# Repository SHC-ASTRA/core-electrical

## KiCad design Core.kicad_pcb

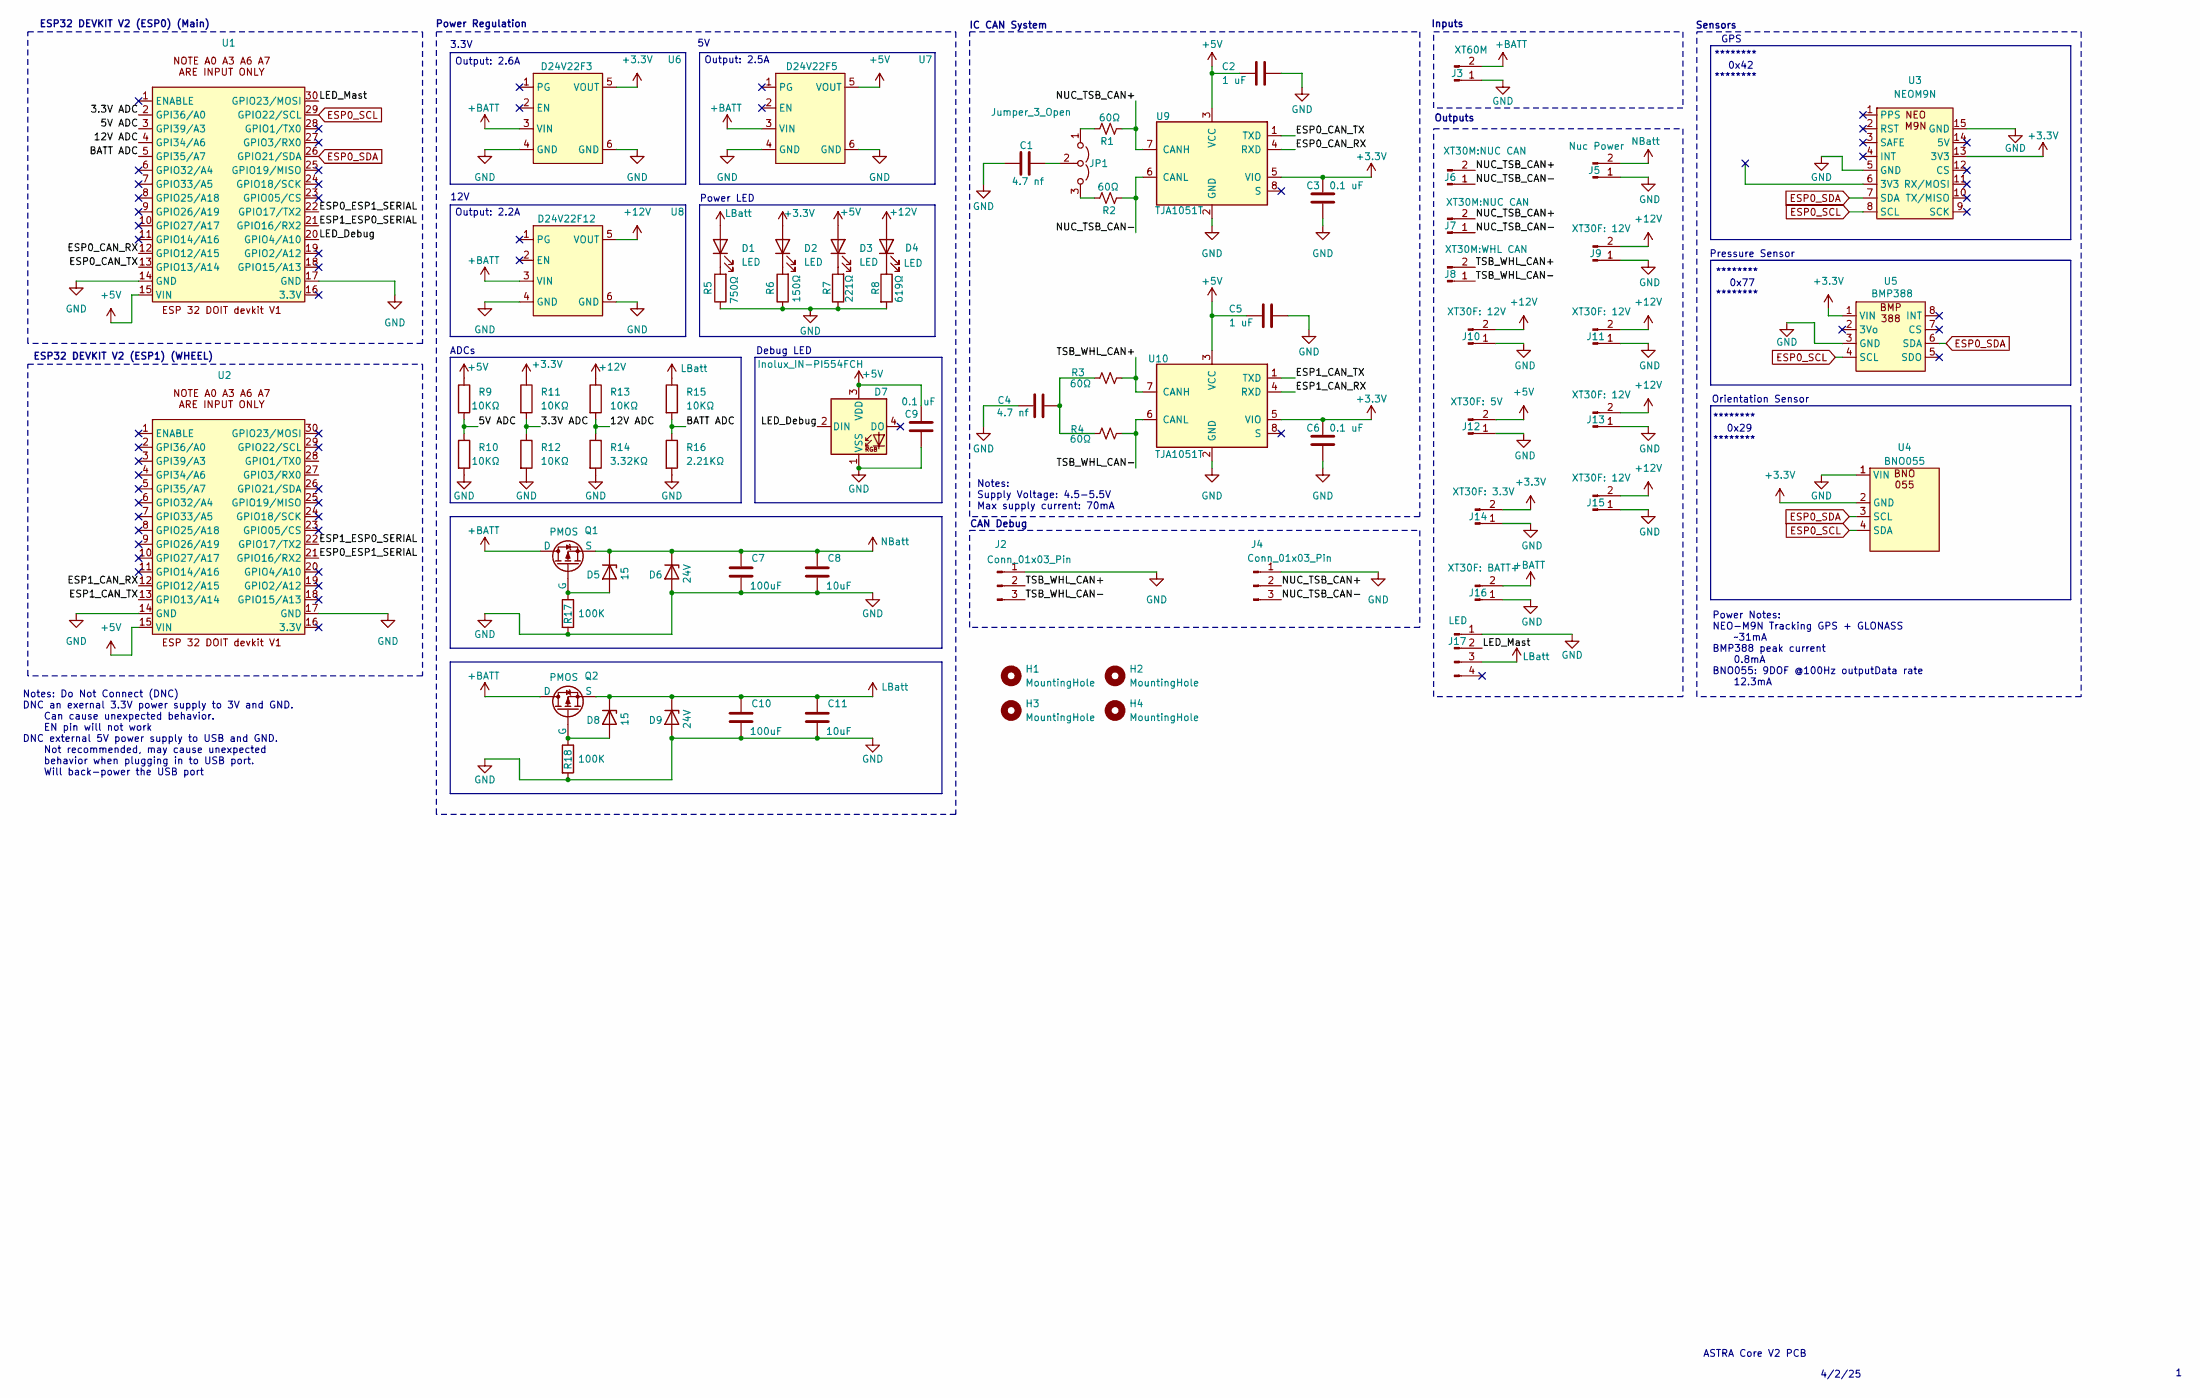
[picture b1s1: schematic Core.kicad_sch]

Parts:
C1, C4: 4.7 nf; C_0603_1608Metric_Pad1.08x0.95mm_HandSolder
C2, C5: 1 uF; C_0603_1608Metric_Pad1.08x0.95mm_HandSolder
C3, C6, C9: 0.1 uF; C_0603_1608Metric_Pad1.08x0.95mm_HandSolder
C7, C10: 100uF; C_0603_1608Metric_Pad1.08x0.95mm_HandSolder
C8, C11: 10uF; C_0603_1608Metric_Pad1.08x0.95mm_HandSolder
D1, D2, D3, D4: LED; LED 3mm
D5, D8: 15; D_SOD-123
D6, D9: 24V; TVS_CUHZ20VH3F
D7: Inolux_IN-PI554FCH; LED_Inolux_IN-PI554FCH_PLCC4_5.0x5.0mm_P3.2mm
H1, H2, H3, H4: MountingHole; 3mm Hole
J2, J4: Conn_01x03_Pin; PinHeader_1x03_P2.54mm_Vertical
J3: XT60M; AMASS_XT60PW-M_1x02_P7.20mm_Horizontal
J5: Nuc Power; Molex_Mini-Fit_Jr_5569-02A2_2x01_P4.20mm_Horizontal
J6, J7: XT30M:NUC CAN; XT30M_MODIFIED
J8: XT30M:WHL CAN; XT30M_MODIFIED
J9, J10, J11, J13, J15: XT30F: 12V; XT30F_MODIFIED
J12: XT30F: 5V; XT30F_MODIFIED
J14: XT30F: 3.3V; XT30F_MODIFIED
J16: XT30F: BATT+; XT30F_MODIFIED
J17: LED; Molex_Mini-Fit_Jr__2x02_Horizontal
JP1: Jumper_3_Open; PinHeader_1x03_P2.54mm_Vertical
Q1, Q2: PMOS; TO-252-2
R1, R2, R3, R4: 60Ω; R_0603_1608Metric_Pad0.98x0.95mm_HandSolder
R5: 750Ω; R_0603_1608Metric_Pad0.98x0.95mm_HandSolder
R6: 150Ω; R_0603_1608Metric_Pad0.98x0.95mm_HandSolder
R7: 221Ω; R_0603_1608Metric_Pad0.98x0.95mm_HandSolder
R8: 619Ω; R_0603_1608Metric_Pad0.98x0.95mm_HandSolder
R9, R10, R11, R12, R13, R15: 10KΩ; R_0603_1608Metric_Pad0.98x0.95mm_HandSolder
R14: 3.32KΩ; R_0603_1608Metric_Pad0.98x0.95mm_HandSolder
R16: 2.21KΩ; R_0603_1608Metric_Pad0.98x0.95mm_HandSolder
R17, R18: 100K; C_0603_1608Metric_Pad1.08x0.95mm_HandSolder
U1, U2: esp32_devkit_v1
U3: NEOM9N; NEO-M9N
U4: BNO055; Molex_Mini-Fit_Jr__2x02_Horizontal
U5: BMP388
U6: D24V22F3; D24V22Fx
U7: D24V22F5; D24V22Fx
U8: D24V22F12; D24V22Fx
U9, U10: TJA1051T; SOIC-8_3.9x4.9mm_P1.27mm

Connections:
+3.3V: C3.1, C6.1, D2.2 (A), J14.2 (Pin_1), R11.1, U3.13 (3V3), U4.2 (GND), U5.1 (VIN), U6.5 (VOUT), U9.5 (VIO), U10.5 (VIO)
+5V: C2.2, C5.2, C9.1, D3.2 (A), D7.3 (VDD), J12.2 (Pin_1), R9.1, U1.15 (VIN), U2.15 (VIN), U7.5 (VOUT), U9.3 (VCC), U10.3 (VCC)
+12V: D4.2 (A), J9.2 (Pin_1), J10.2 (Pin_1), J11.2 (Pin_1), J13.2 (Pin_1), J15.2 (Pin_1), R13.1, U8.5 (VOUT)
+BATT: J3.2 (Pin_1), J16.2 (Pin_1), Q1.1 (D), Q2.1 (D), U6.3 (VIN), U7.3 (VIN), U8.3 (VIN)
/3.3V ADC: R11.2, R12.1, U1.2 (GPI36/A0)
/5V ADC: R9.2, R10.1, U1.3 (GPI39/A3)
/12V ADC: R13.2, R14.1, U1.4 (GPI34/A6)
/BATT ADC: R15.2, R16.1, U1.5 (GPI35/A7)
/ESP0_CAN_RX: U1.12 (GPIO12/A15), U9.4 (RXD)
/ESP0_CAN_TX: U1.13 (GPIO13/A14), U9.1 (TXD)
/ESP0_ESP1_SERIAL: U1.22 (GPIO17/TX2), U2.21 (GPIO16/RX2)
/ESP1_CAN_RX: U2.12 (GPIO12/A15), U10.4 (RXD)
/ESP1_CAN_TX: U2.13 (GPIO13/A14), U10.1 (TXD)
/ESP1_ESP0_SERIAL: U1.21 (GPIO16/RX2), U2.22 (GPIO17/TX2)
/LED_Debug: D7.2 (DIN), U1.20 (GPIO4/A10)
/LED_Mast: J17.2, U1.30 (GPIO23/MOSI)
/NUC_TSB_CAN+: J4.2, J6.2 (Pin_1), J7.2 (Pin_1), R1.1, U9.7 (CANH)
/NUC_TSB_CAN-: J4.3, J6.1 (Pin_2), J7.1 (Pin_2), R2.2, U9.6 (CANL)
/TSB_WHL_CAN+: J2.2, J8.2 (Pin_1), R3.1, U10.7 (CANH)
/TSB_WHL_CAN-: J2.3, J8.1 (Pin_2), R4.2, U10.6 (CANL)
ESP0_SCL: U1.29 (GPIO22/SCL), U3.8 (SCL), U4.4 (SDA), U5.4 (SCL)
ESP0_SDA: U1.26 (GPIO21/SDA), U3.7 (SDA), U4.3 (SCL), U5.6 (SDA)
GND: C1.1, C2.1, C3.2, C4.1, C5.1, C6.2, C7.2, C8.2, C9.2, C10.2, C11.2, D6.2 (A), D7.1 (VSS), D9.2 (A), J2.1, J3.1 (Pin_2), J4.1, J5.1 (Pin_2), J9.1 (Pin_2), J10.1 (Pin_2), J11.1 (Pin_2), J12.1 (Pin_2), J13.1 (Pin_2), J14.1 (Pin_2), J15.1 (Pin_2), J16.1 (Pin_2), J17.1, R5.1, R6.1, R7.1, R8.2, R10.2, R12.2, R14.2, R16.2, R17.2, R18.2, U1.14 (GND), U1.17 (GND), U2.14 (GND), U2.17 (GND), U3.5 (GND), U3.15 (GND), U4.1 (VIN), U5.3 (GND), U6.4 (GND), U6.6 (GND), U7.4 (GND), U7.6 (GND), U8.4 (GND), U8.6 (GND), U9.2 (GND), U10.2 (GND)
LBatt: C10.1, C11.1, D1.2 (A), D8.1 (K), D9.1 (K), J17.3, Q2.3 (S), R15.1
NBatt: C7.1, C8.1, D5.1 (K), D6.1 (K), J5.2 (Pin_1), Q1.3 (S)
unnamed: C4.2, R3.2, R4.1
unnamed: D1.1 (K), R5.2
unnamed: D2.1 (K), R6.2
unnamed: D3.1 (K), R7.2
unnamed: D4.1 (K), R8.1
unnamed: D5.2 (A), Q1.2 (G), R17.1
unnamed: D8.2 (A), Q2.2 (G), R18.1
unnamed: JP1.1 (A), R1.2
unnamed: JP1.3 (B), R2.1
unnamed: C1.2, JP1.2 (C)

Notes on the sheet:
******** 0x29 ********
ASTRA Core V2 PCB
ESP32 DEVKIT V2 (ESP0) (Main)
IC CAN System
Power Notes: NEO-M9N Tracking GPS + GLONASS ~31mA BMP388 peak current 0.8mA BNO055: 9DOF @100Hz outputData rate 12.3mA
ESP32 DEVKIT V2 (ESP1) (WHEEL)
Output: 2.2A
Output: 2.5A
Power Regulation
******** 0x42 ********
Orientation Sensor
Outputs
Debug LED
Notes: Supply Voltage: 4.5-5.5V Max supply current: 70mA
3.3V
GPS
ADCs
Sensors
12V
Pressure Sensor
******** 0x77 ********
CAN Debug
Notes: Do Not Connect (DNC) DNC an exernal 3.3V power supply to 3V and GND. Can cause unexpected behavior. EN pin will not work DNC external 5V power supply to USB and GND. Not recommended, may cause unexpected behavior when plugging in to USB port. Will back-power the USB port
Inputs
Output: 2.6A
4/2/25
Power LED

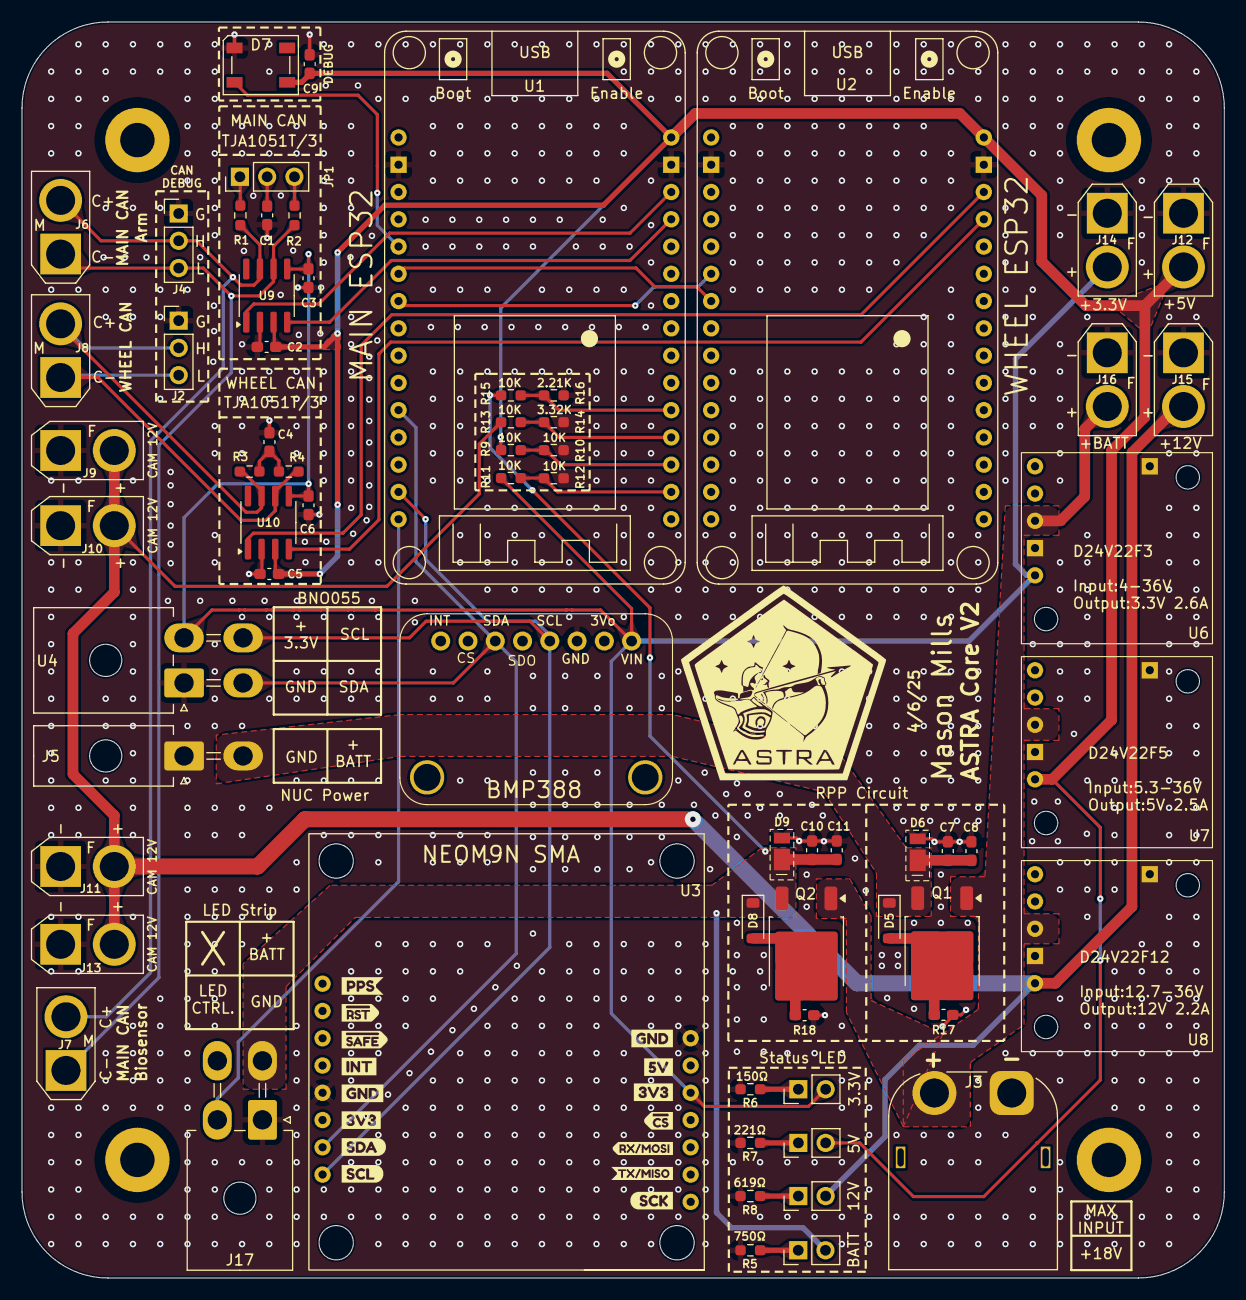
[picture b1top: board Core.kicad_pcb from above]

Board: 2 copper layers, 112.0 x 117.0 mm, 71 parts (0 on the bottom side), 35 nets.

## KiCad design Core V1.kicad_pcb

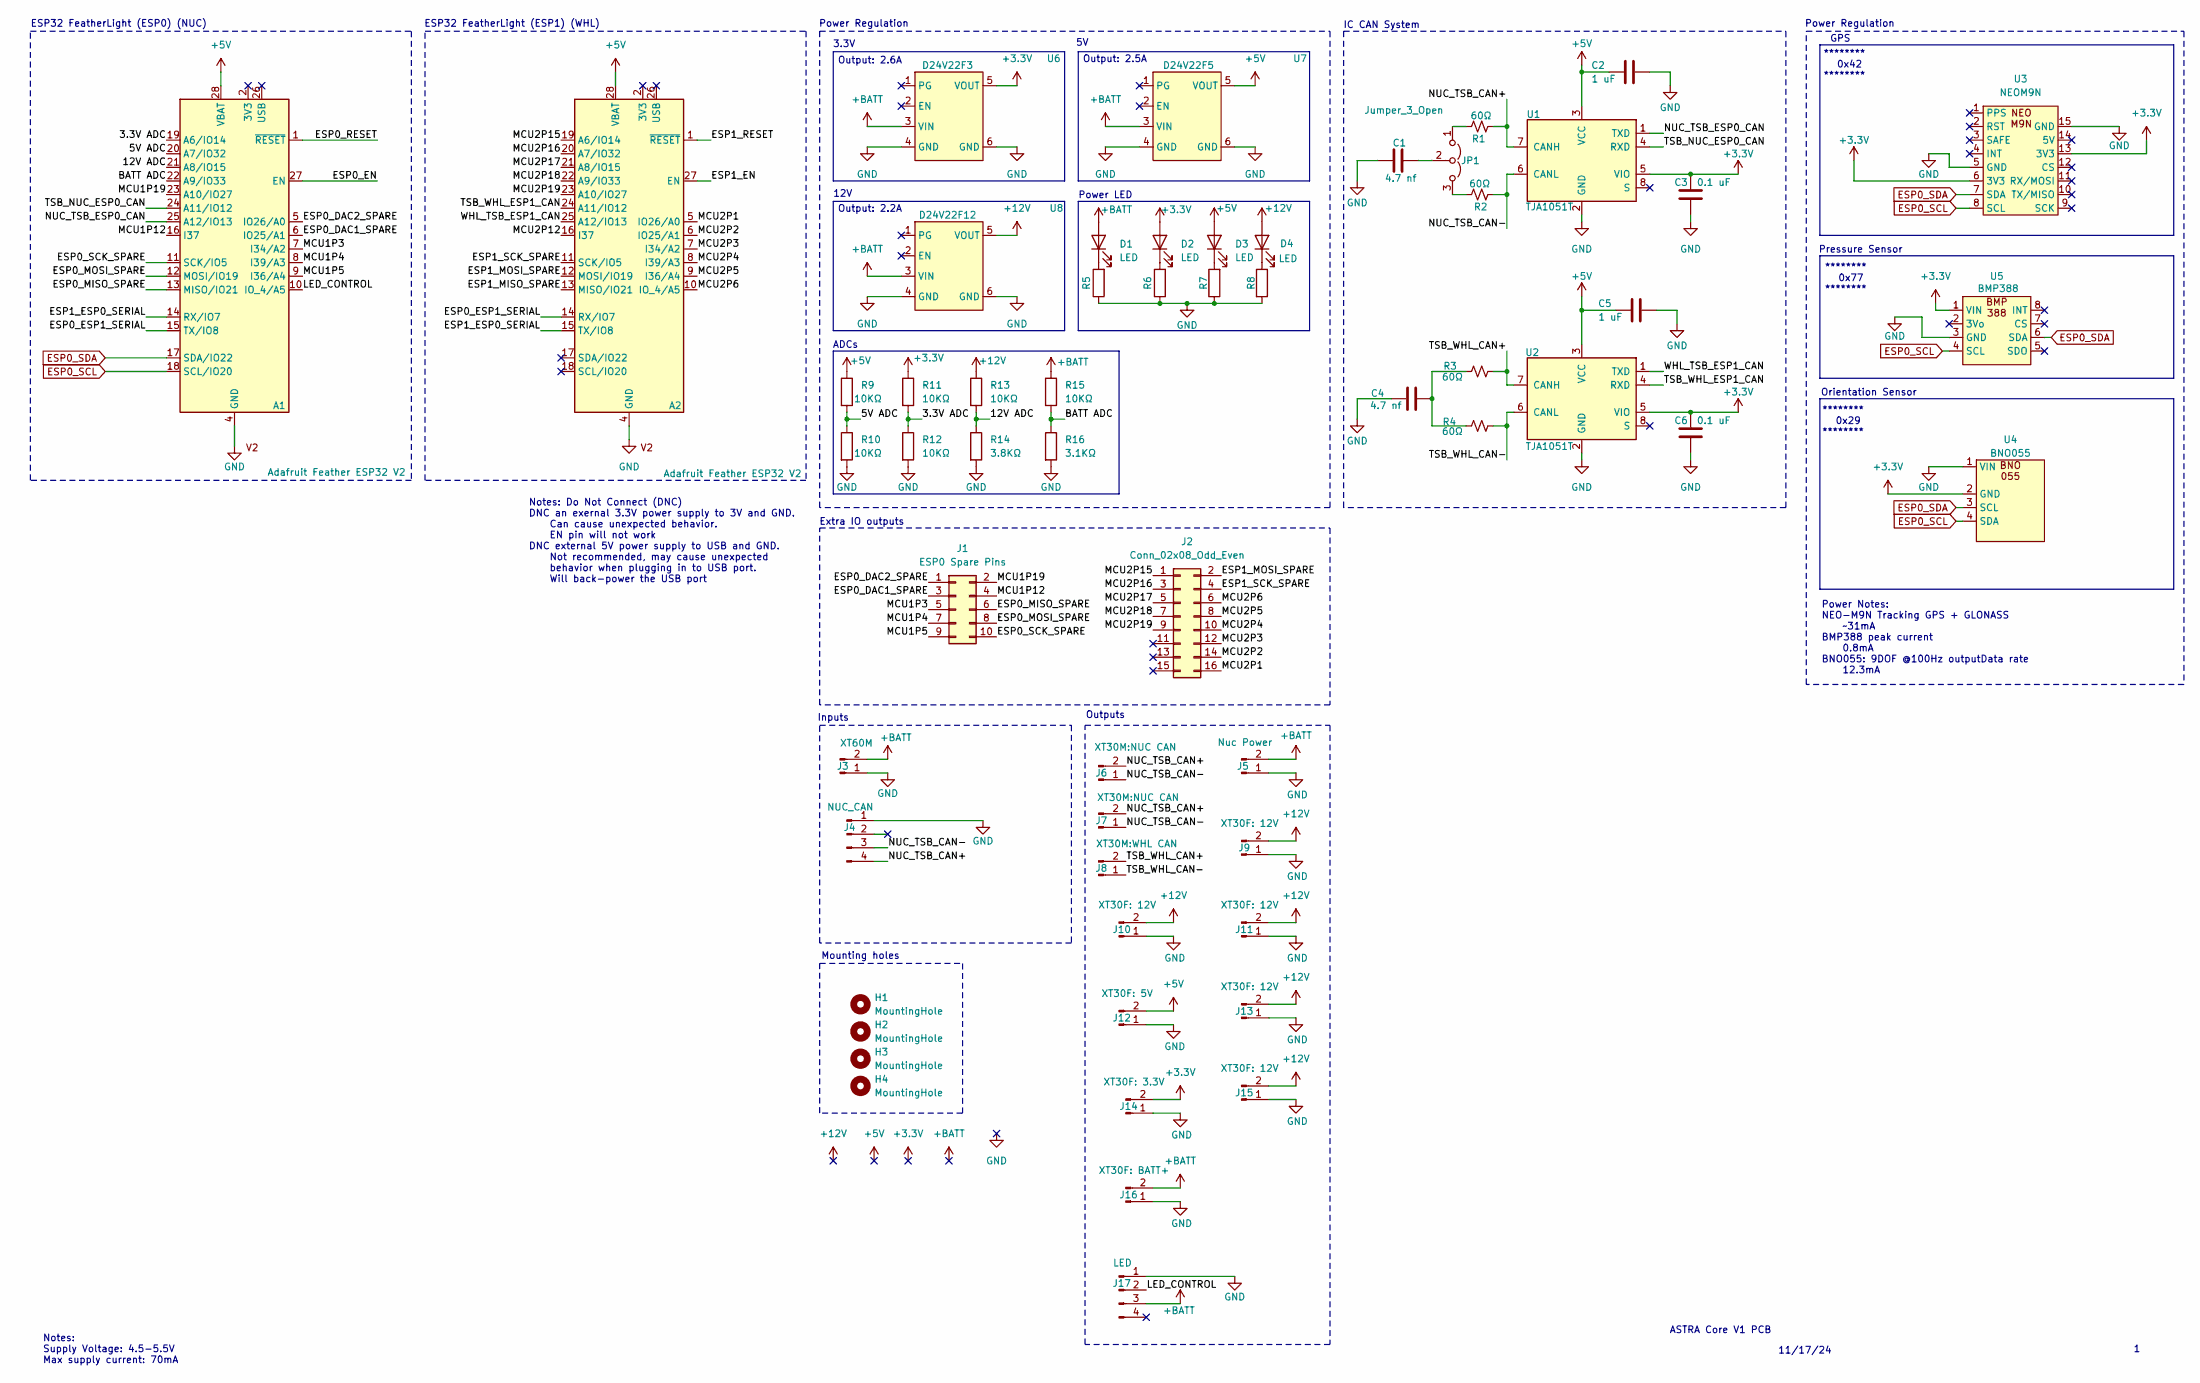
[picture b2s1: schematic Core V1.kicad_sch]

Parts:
A1, A2: Adafruit Feather ESP32 V2; Adafruit_Feather_WithMountingHoles
C1, C4: 4.7 nf; C_0603_1608Metric_Pad1.08x0.95mm_HandSolder
C2, C5: 1 uF; C_0603_1608Metric_Pad1.08x0.95mm_HandSolder
C3, C6: 0.1 uF; C_0603_1608Metric_Pad1.08x0.95mm_HandSolder
D1, D2, D3, D4: LED; LED 3mm
H1, H2, H3, H4: MountingHole; MountingHole_3.2mm_M3
J1: ESP0 Spare Pins; PinHeader_2x05_P2.54mm_Vertical
J2: Conn_02x08_Odd_Even; PinHeader_2x08_P2.54mm_Vertical
J3: XT60M; AMASS_XT60PW-M_1x02_P7.20mm_Horizontal
J4: NUC_CAN; Molex_Mini-Fit_Jr__2x02_Horizontal
J5: Nuc Power; Molex_Mini-Fit_Jr_5569-02A2_2x01_P4.20mm_Horizontal
J6, J7: XT30M:NUC CAN; XT30M_MODIFIED
J8: XT30M:WHL CAN; XT30M_MODIFIED
J9, J10, J11, J13, J15: XT30F: 12V; XT30F_MODIFIED
J12: XT30F: 5V; XT30F_MODIFIED
J14: XT30F: 3.3V; XT30F_MODIFIED
J16: XT30F: BATT+; XT30F_MODIFIED
J17: LED; Molex_Mini-Fit_Jr__2x02_Horizontal
JP1: Jumper_3_Open; PinHeader_1x03_P2.54mm_Vertical
R1, R2, R3, R4: 60Ω; R_0603_1608Metric_Pad0.98x0.95mm_HandSolder
R5, R6, R7, R8, R14: 3.8KΩ; R_0603_1608Metric_Pad0.98x0.95mm_HandSolder
R9, R10, R11, R12, R13, R15: 10KΩ; R_0603_1608Metric_Pad0.98x0.95mm_HandSolder
R16: 3.1KΩ; R_0603_1608Metric_Pad0.98x0.95mm_HandSolder
U1, U2: TJA1051T; SOIC-8_3.9x4.9mm_P1.27mm
U3: NEOM9N; NEO-M9N
U4: BNO055; Molex_Mini-Fit_Jr__2x02_Horizontal
U5: BMP388
U6: D24V22F3; D24V22Fx
U7: D24V22F5; D24V22Fx
U8: D24V22F12; D24V22Fx

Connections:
+3.3V: C3.1, C6.1, D2.2 (A), J14.2 (Pin_1), R11.1, U1.5 (VIO), U2.5 (VIO), U3.6 (3V3), U3.13 (3V3), U4.2 (GND), U5.1 (VIN), U6.5 (VOUT)
+5V: A1.28 (VBAT), A2.28 (VBAT), C2.2, C5.2, D3.2 (A), J12.2 (Pin_1), R9.1, U1.3 (VCC), U2.3 (VCC), U7.5 (VOUT)
+12V: D4.2 (A), J9.2 (Pin_1), J10.2 (Pin_1), J11.2 (Pin_1), J13.2 (Pin_1), J15.2 (Pin_1), R13.1, U8.5 (VOUT)
+BATT: D1.2 (A), J3.2 (Pin_1), J5.2 (Pin_1), J16.2 (Pin_1), J17.3, R15.1, U6.3 (VIN), U7.3 (VIN), U8.3 (VIN)
/3.3V ADC: A1.19 (A6/IO14), R11.2, R12.1
/5V ADC: A1.20 (A7/IO32), R9.2, R10.1
/12V ADC: A1.21 (A8/IO15), R13.2, R14.1
/BATT ADC: A1.22 (A9/IO33), R15.2, R16.1
/ESP0_DAC1_SPARE: A1.6 (IO25/A1), J1.3
/ESP0_DAC2_SPARE: A1.5 (IO26/A0), J1.1
/ESP0_EN: A1.27 (EN)
/ESP0_ESP1_SERIAL: A1.15 (TX/IO8), A2.14 (RX/IO7)
/ESP0_MISO_SPARE: A1.13 (MISO/IO21), J1.6
/ESP0_MOSI_SPARE: A1.12 (MOSI/IO19), J1.8
/ESP0_RESET: A1.1 (~RESET)
/ESP0_SCK_SPARE: A1.11 (SCK/IO5), J1.10
/ESP1_EN: A2.27 (EN)
/ESP1_ESP0_SERIAL: A1.14 (RX/IO7), A2.15 (TX/IO8)
/ESP1_MISO_SPARE: A2.13 (MISO/IO21)
/ESP1_MOSI_SPARE: A2.12 (MOSI/IO19), J2.2
/ESP1_RESET: A2.1 (~RESET)
/ESP1_SCK_SPARE: A2.11 (SCK/IO5), J2.4
/LED_CONTROL: A1.10 (IO_4/A5), J17.2
/MCU1P3: A1.7 (I34/A2), J1.5
/MCU1P4: A1.8 (I39/A3), J1.7
/MCU1P5: A1.9 (I36/A4), J1.9
/MCU1P12: A1.16 (I37), J1.4
/MCU1P19: A1.23 (A10/IO27), J1.2
/MCU2P1: A2.5 (IO26/A0), J2.16
/MCU2P2: A2.6 (IO25/A1), J2.14
/MCU2P3: A2.7 (I34/A2), J2.12
/MCU2P4: A2.8 (I39/A3), J2.10
/MCU2P5: A2.9 (I36/A4), J2.8
/MCU2P6: A2.10 (IO_4/A5), J2.6
/MCU2P12: A2.16 (I37)
/MCU2P15: A2.19 (A6/IO14), J2.1
/MCU2P16: A2.20 (A7/IO32), J2.3
/MCU2P17: A2.21 (A8/IO15), J2.5
/MCU2P18: A2.22 (A9/IO33), J2.7
/MCU2P19: A2.23 (A10/IO27), J2.9
/NUC_TSB_CAN+: J4.4, J6.2 (Pin_1), J7.2 (Pin_1), R1.1, U1.7 (CANH)
/NUC_TSB_CAN-: J4.3, J6.1 (Pin_2), J7.1 (Pin_2), R2.2, U1.6 (CANL)
/NUC_TSB_ESP0_CAN: A1.25 (A12/IO13), U1.1 (TXD)
/TSB_NUC_ESP0_CAN: A1.24 (A11/IO12), U1.4 (RXD)
/TSB_WHL_CAN+: J8.2 (Pin_1), R3.1, U2.7 (CANH)
/TSB_WHL_CAN-: J8.1 (Pin_2), R4.2, U2.6 (CANL)
/TSB_WHL_ESP1_CAN: A2.24 (A11/IO12), U2.4 (RXD)
/WHL_TSB_ESP1_CAN: A2.25 (A12/IO13), U2.1 (TXD)
ESP0_SCL: A1.18 (SCL/IO20), U3.8 (SCL), U4.4 (SDA), U5.4 (SCL)
ESP0_SDA: A1.17 (SDA/IO22), U3.7 (SDA), U4.3 (SCL), U5.6 (SDA)
GND: A1.4 (GND), A2.4 (GND), C1.1, C2.1, C3.2, C4.1, C5.1, C6.2, J3.1 (Pin_2), J4.1, J5.1 (Pin_2), J9.1 (Pin_2), J10.1 (Pin_2), J11.1 (Pin_2), J12.1 (Pin_2), J13.1 (Pin_2), J14.1 (Pin_2), J15.1 (Pin_2), J16.1 (Pin_2), J17.1, R5.1, R6.1, R7.1, R8.2, R10.2, R12.2, R14.2, R16.2, U1.2 (GND), U2.2 (GND), U3.5 (GND), U3.15 (GND), U4.1 (VIN), U5.3 (GND), U6.4 (GND), U6.6 (GND), U7.4 (GND), U7.6 (GND), U8.4 (GND), U8.6 (GND)
unnamed: C4.2, R3.2, R4.1
unnamed: D1.1 (K), R5.2
unnamed: D2.1 (K), R6.2
unnamed: D3.1 (K), R7.2
unnamed: D4.1 (K), R8.1
unnamed: JP1.1 (A), R1.2
unnamed: JP1.3 (B), R2.1
unnamed: C1.2, JP1.2 (C)

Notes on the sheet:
******** 0x29 ********
ASTRA Core V1 PCB
ESP32 FeatherLight (ESP0) (NUC)
IC CAN System
Power Notes: NEO-M9N Tracking GPS + GLONASS ~31mA BMP388 peak current 0.8mA BNO055: 9DOF @100Hz outputData rate 12.3mA
ESP32 FeatherLight (ESP1) (WHL)
Output: 2.2A
Output: 2.5A
Power Regulation
******** 0x42 ********
Orientation Sensor
Outputs
Notes: Supply Voltage: 4.5-5.5V Max supply current: 70mA
3.3V
GPS
Extra IO outputs
ADCs
12V
Mounting holes
Pressure Sensor
******** 0x77 ********
Notes: Do Not Connect (DNC) DNC an exernal 3.3V power supply to 3V and GND. Can cause unexpected behavior. EN pin will not work DNC external 5V power supply to USB and GND. Not recommended, may cause unexpected behavior when plugging in to USB port. Will back-power the USB port
Inputs
Output: 2.6A
11/17/24
Power LED

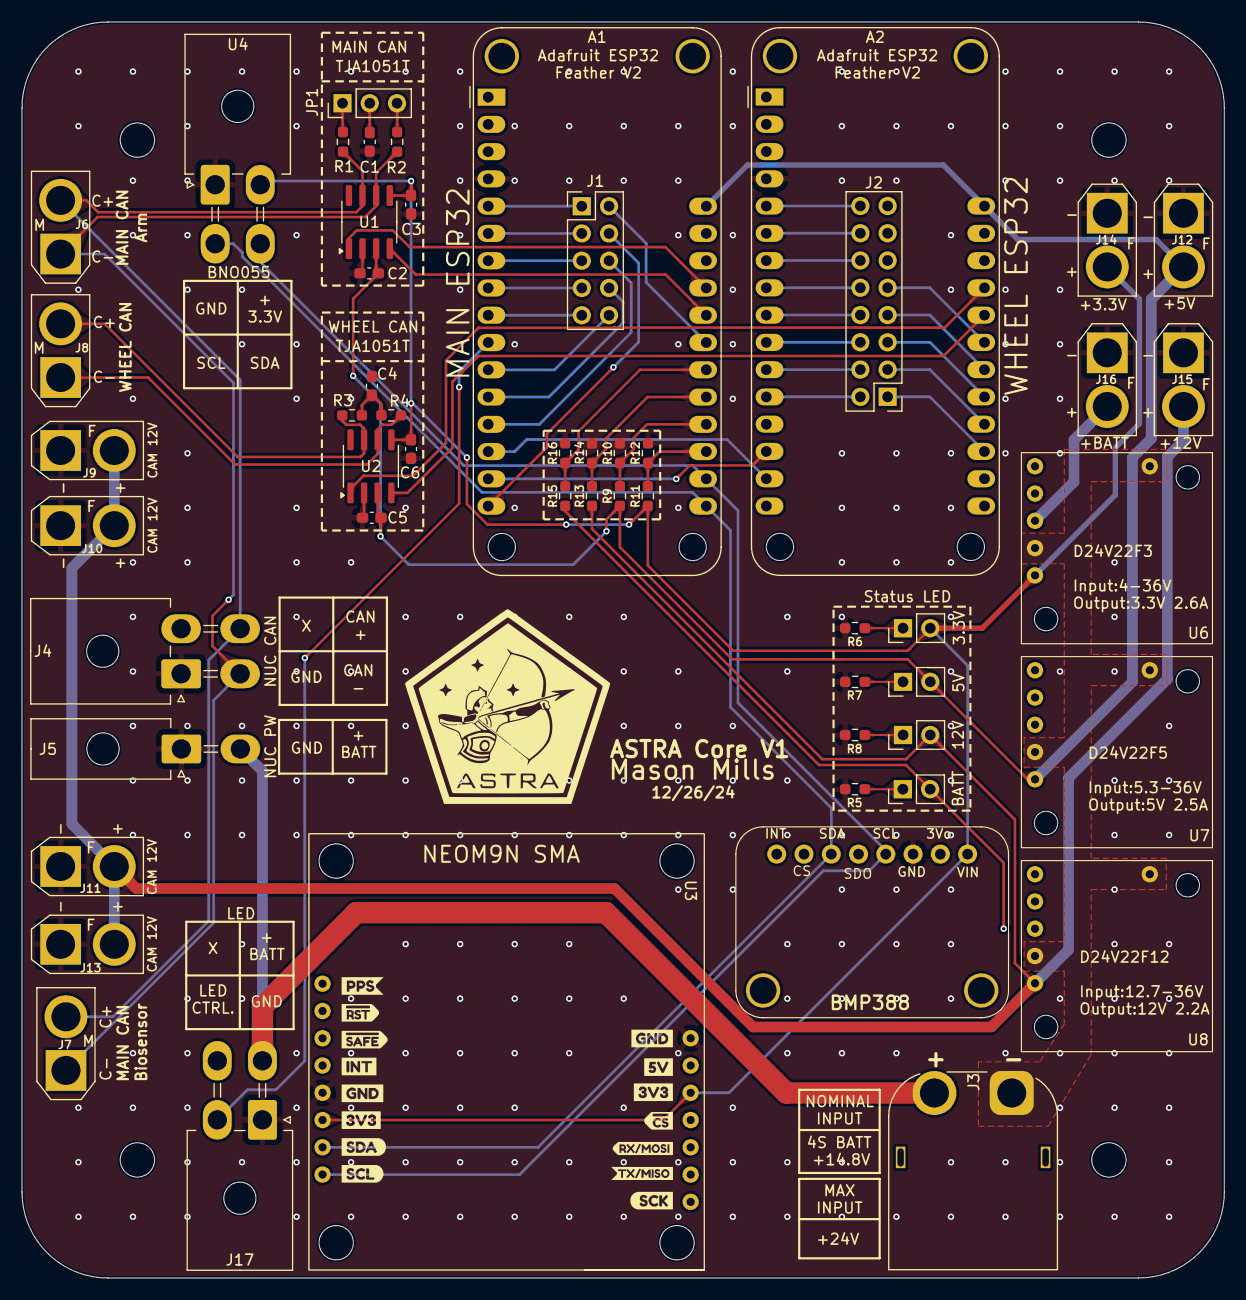
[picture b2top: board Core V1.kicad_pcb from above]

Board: 2 copper layers, 112.0 x 117.0 mm, 58 parts (0 on the bottom side), 53 nets.

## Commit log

2025-08-26 Original schematic from 2020 :astonished:
2025-08-26 From 3/17/22
2025-08-26 From URC '24
2025-08-26 From URC '25, V1
2025-08-26 From URC '25, V2
